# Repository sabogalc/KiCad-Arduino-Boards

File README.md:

# KiCad Arduino Boards

## Introduction
This repository contains KiCad version 8 design files for eight different Arduino boards that have been recreated from scratch. I was first inspired to work on this project when I received an Arduino Uno R3 for a class project (which you can read [here](https://github.com/sabogalc/KiCad-Arduino-Boards/blob/main/Remote%20Temperature%20Monitoring%20Project.pdf)). Although I had never used an Arduino before, I found it quite useful and versatile. However, I wanted to make some changes to better suit my needs.

## Project Motivation
While working with the Arduino Uno R3, I was frustrated by the need for a USB-B printer cable to use it. Since the Arduino hardware is open source, I decided to recreate the board with a USB-C connector. Additionally, I learned that Arduino boards are not made in KiCad, so I figured this project could also have another benefit in making the designs more open and accessible. Although buying an R4 Minima that already comes with USB-C would have been easier and less expensive, I enjoyed the challenge of re-designing the board myself.

## Design Process
Every Adruino board I could find is made in either EAGLE or Altium, and KiCad has importers for both of these formats. However, importing designs always comes with a level of artifacting and other inaccuracies. The effort to correct the imports would be comparable to remaking the board from scratch, so I opted for the latter since it would produce a cleaner end result. 

Given the popularity and open-source nature of Arduino boards, I assumed that partial or complete KiCad versions might already exist. The following repositories were helpful for getting started:
- [Arduino Uno R3 From Scratch](https://github.com/rheingoldheavy/arduino_uno_r3_from_scratch): Schematic and BOM
- [Arduino Uno KiCad Template](https://github.com/Jeff-Russ/Arduino_Uno_Template): Bare board layout
- [Arduino UNO R3 BOM](https://gist.github.com/yahyatawil/ee6ad731bcf5a5b37dcf2cac04245fbe): BOM only

Even with these resources, I had to find a reset switch footprint myself, but eventually I landed on a compatible one with the TS06-667-30-BK-100-G-SMT-TR by CUI Devices. I now had every piece I needed to make a schematic and PCB, and while doing the PCB layout I would consistently reference the imported design and try to make the component placement and routing as close to the original as possible.

## Visual Comparison
Below is a comparison of the imported UNO R3 board and my completed board, highlighting the differences and benefits in re-making the board from scratch. The most apparent differences are in the silkscreen labeling and the included 3D models of the components:

## Boards Included
This repository includes designs for:
- Arduino Uno R3
- Arduino Uno R3 SMD
- Arduino Uno R4 Minima
- Arduino Uno R4 WiFi (this one may have some issues; see its folder for details)
- Arduino Leonardo
- Arduino Micro
- Arduino Nano
- Arduino Mega 2560

For details about each board, refer to the `README` file in their respective folders.

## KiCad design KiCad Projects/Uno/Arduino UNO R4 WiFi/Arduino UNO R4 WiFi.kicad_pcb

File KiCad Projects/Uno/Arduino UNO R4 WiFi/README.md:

# UNO R4 WiFi
I am not the same man I was before making this board.

As soon as I saw the 96 LED array on this board, I knew that I would be in for some work, and of all the boards in this repository, this is the only one that I am not confident would pass a fabricator's specifications. I will highlight the parts of this board that I think may be problematic below.

Firstly, the 3.3V fuse is extremely close to a GND pad on the USB-C port, which could be a possible weak point for a 3.3V short to GND to happen.

Next of course is the placement and routing of the LEDs, especially because lots of these tracks have very little clearance between them.

Some of the curved traces on this board may also be problematic, like in the example below.

All in all, if anyone does actually order the gerbers for this board, please let me know if either all is well or if there are corrections that need to be made.

Below are the screenshots of this board from KiCad's 3D board viewer.

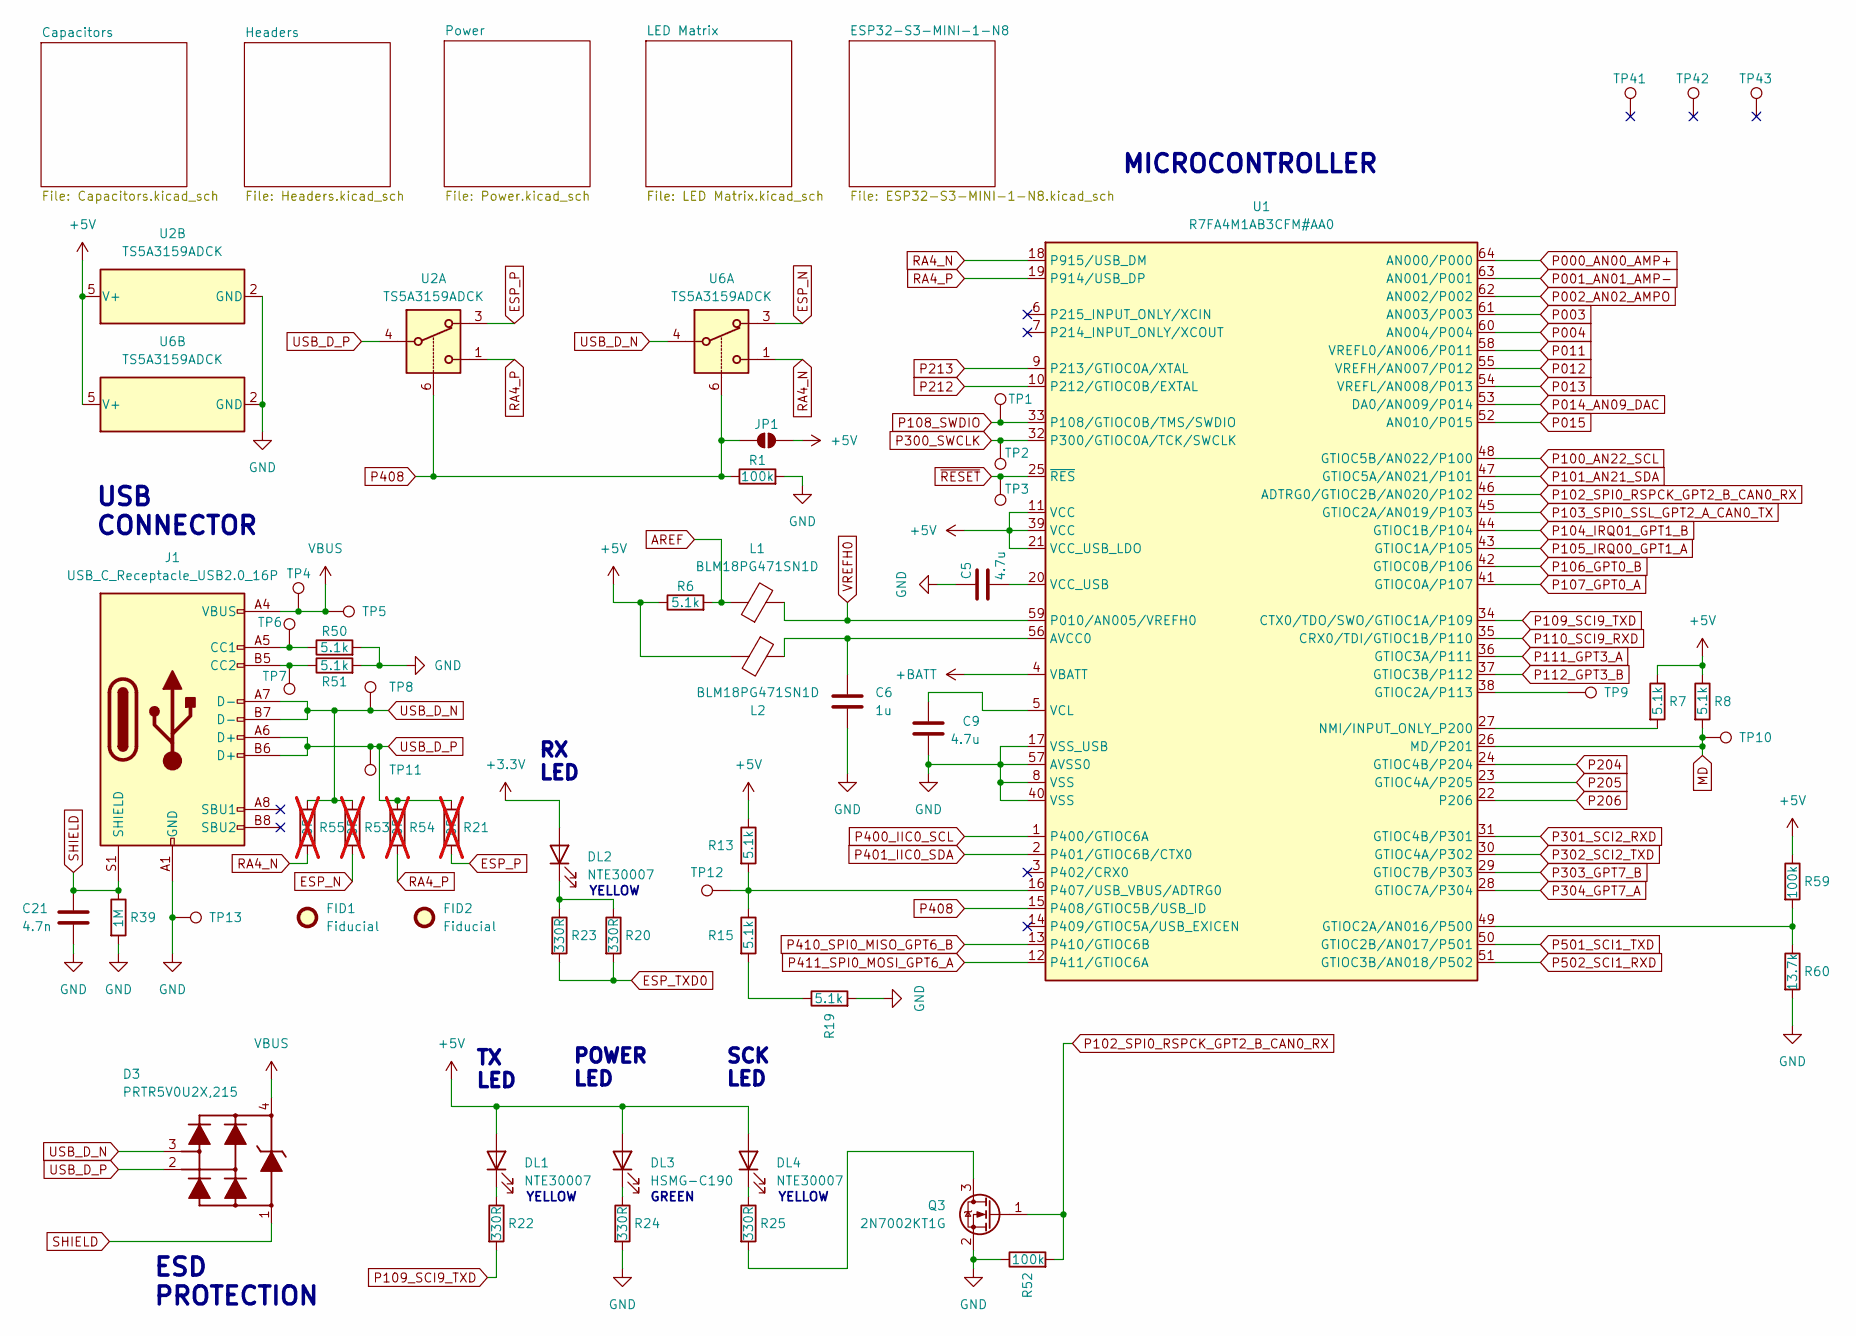
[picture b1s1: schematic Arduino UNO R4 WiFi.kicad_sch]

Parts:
C5, C9: 4.7u; C_0603_1608Metric
C6: 1u; C_0402_1005Metric
C21: 4.7n; C_0805_2012Metric
D3: PRTR5V0U2X,215; SOT-143
DL1, DL2, DL4: NTE30007; LED_0603_1608Metric
DL3: HSMG-C190; LED_0603_1608Metric
FID1, FID2: Fiducial; Fiducial_1mm_Mask2mm
J1: USB_C_Receptacle_USB2.0_16P; USB_C_Receptacle_GCT_USB4105-xx-A_16P_TopMnt_Horizontal
JP1: SolderJumper_2_Open; SolderJumper-2_P1.3mm_Open_Pad1.0x1.5mm
L1, L2: BLM18PG471SN1D; L_0603_1608Metric
Q3: 2N7002KT1G; SC-59
R1, R52, R59: 100k; R_0402_1005Metric
R6, R7, R8, R13, R15, R19, R50, R51: 5.1k; R_0402_1005Metric
R20, R22, R23, R24, R25: 330R; R_0402_1005Metric
R21, R53, R54, R55: 0R; R_0402_1005Metric; not fitted
R39: 1M; R_0402_1005Metric
R60: 13.7k; R_0402_1005Metric
TP1, TP2, TP3, TP4, TP6, TP7, TP10, TP12: TestPoint; TestPoint_Pad_D0.8mm
TP5, TP8, TP11, TP13, TP41, TP42, TP43: TestPoint; TestPoint_Pad_D1.0mm
TP9: TestPoint; TestPoint_P113
U1: R7FA4M1AB3CFM#AA0; LQFP-64_10x10mm_P0.5mm
U2, U6: TS5A3159ADCK; SOT-363_SC-70-6

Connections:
+3.3V: DL2.2 (A); also elsewhere on the board
+5V: DL1.2 (A), DL3.2 (A), DL4.2 (A), JP1.2 (B), L2.2, R6.1, R7.1, R8.1, R13.1, R59.1, U1.11 (VCC), U1.21 (VCC_USB_LDO), U1.39 (VCC), U2.5 (V+), U6.5 (V+); also elsewhere on the board
+BATT: U1.4 (VBATT); also elsewhere on the board
AREF: L1.1, R6.2; also elsewhere on the board
ESP_N: R53.2, U6.3; also elsewhere on the board
ESP_P: R21.2, U2.3; also elsewhere on the board
ESP_TXD0: R20.2, R23.2; also elsewhere on the board
GND: C5.2, C6.2, C9.1, C21.2, J1.A1 (GND), J1.A12 (GND), J1.B1 (GND), J1.B12 (GND), Q3.2 (S), R1.2, R19.2, R24.2, R39.2, R50.2, R51.2, R52.1, R60.2, TP13.1, U1.8 (VSS), U1.17 (VSS_USB), U1.40 (VSS), U1.57 (AVSS0), U2.2 (GND), U6.2 (GND); also elsewhere on the board
MD: R8.2, TP10.1, U1.26 (MD/P201); also elsewhere on the board
unnamed: DL1.1 (K), R22.1
unnamed: DL2.1 (K), R20.1, R23.1
unnamed: DL3.1 (K), R24.1
unnamed: DL4.1 (K), R25.1
unnamed: J1.A5 (CC1), R50.1, TP6.1
unnamed: J1.B5 (CC2), R51.1, TP7.1
unnamed: Q3.3 (D), R25.2
unnamed: R15.2, R19.1
unnamed: C6.1, L2.1, U1.56 (AVCC0)
unnamed: R59.2, R60.1, U1.49 (GTIOC2A/AN016/P500)
unnamed: TP9.1, U1.38 (GTIOC2A/P113)
unnamed: R7.2, U1.27 (NMI/INPUT_ONLY_P200)
unnamed: R13.2, R15.1, TP12.1, U1.16 (P407/USB_VBUS/ADTRG0)
unnamed: C5.1, U1.20 (VCC_USB)
unnamed: C9.2, U1.5 (VCL)
P000_AN00_AMP+: U1.64 (AN000/P000); also elsewhere on the board
P001_AN01_AMP-: U1.63 (AN001/P001); also elsewhere on the board
P002_AN02_AMPO: U1.62 (AN002/P002); also elsewhere on the board
P003: U1.61 (AN003/P003); also elsewhere on the board
P004: U1.60 (AN004/P004); also elsewhere on the board
P011: U1.58 (VREFL0/AN006/P011); also elsewhere on the board
P012: U1.55 (VREFH/AN007/P012); also elsewhere on the board
P013: U1.54 (VREFL/AN008/P013); also elsewhere on the board
P014_AN09_DAC: U1.53 (DA0/AN009/P014); also elsewhere on the board
P015: U1.52 (AN010/P015); also elsewhere on the board
P100_AN22_SCL: U1.48 (GTIOC5B/AN022/P100); also elsewhere on the board
P101_AN21_SDA: U1.47 (GTIOC5A/AN021/P101); also elsewhere on the board
P102_SPI0_RSPCK_GPT2_B_CAN0_RX: Q3.1 (G), R52.2, U1.46 (ADTRG0/GTIOC2B/AN020/P102); also elsewhere on the board
P103_SPI0_SSL_GPT2_A_CAN0_TX: U1.45 (GTIOC2A/AN019/P103); also elsewhere on the board
P104_IRQ01_GPT1_B: U1.44 (GTIOC1B/P104); also elsewhere on the board
P105_IRQ00_GPT1_A: U1.43 (GTIOC1A/P105); also elsewhere on the board
P106_GPT0_B: U1.42 (GTIOC0B/P106); also elsewhere on the board
P107_GPT0_A: U1.41 (GTIOC0A/P107); also elsewhere on the board
P108_SWDIO: TP1.1, U1.33 (P108/GTIOC0B/TMS/SWDIO); also elsewhere on the board
P109_SCI9_TXD: R22.2, U1.34 (CTX0/TDO/SWO/GTIOC1A/P109); also elsewhere on the board
P110_SCI9_RXD: U1.35 (CRX0/TDI/GTIOC1B/P110); also elsewhere on the board
P111_GPT3_A: U1.36 (GTIOC3A/P111); also elsewhere on the board
P112_GPT3_B: U1.37 (GTIOC3B/P112); also elsewhere on the board
P204: U1.24 (GTIOC4B/P204); also elsewhere on the board
P205: U1.23 (GTIOC4A/P205); also elsewhere on the board
P206: U1.22 (P206); also elsewhere on the board
P212: U1.10 (P212/GTIOC0B/EXTAL); also elsewhere on the board
P213: U1.9 (P213/GTIOC0A/XTAL); also elsewhere on the board
P300_SWCLK: TP2.1, U1.32 (P300/GTIOC0A/TCK/SWCLK); also elsewhere on the board
P301_SCI2_RXD: U1.31 (GTIOC4B/P301); also elsewhere on the board
P302_SCI2_TXD: U1.30 (GTIOC4A/P302); also elsewhere on the board
P303_GPT7_B: U1.29 (GTIOC7B/P303); also elsewhere on the board
P304_GPT7_A: U1.28 (GTIOC7A/P304); also elsewhere on the board
P400_IIC0_SCL: U1.1 (P400/GTIOC6A); also elsewhere on the board
P401_IIC0_SDA: U1.2 (P401/GTIOC6B/CTX0); also elsewhere on the board
P408: JP1.1 (A), R1.1, U1.15 (P408/GTIOC5B/USB_ID), U2.6, U6.6
P410_SPI0_MISO_GPT6_B: U1.13 (P410/GTIOC6B); also elsewhere on the board
P411_SPI0_MOSI_GPT6_A: U1.12 (P411/GTIOC6A); also elsewhere on the board
P501_SCI1_TXD: U1.50 (GTIOC2B/AN017/P501); also elsewhere on the board
P502_SCI1_RXD: U1.51 (GTIOC3B/AN018/P502); also elsewhere on the board
RA4_N: R55.2, U1.18 (P915/USB_DM), U6.1
RA4_P: R54.2, U1.19 (P914/USB_DP), U2.1
SHIELD: C21.1, D3.1, J1.S1 (SHIELD), R39.1
USB_D_N: D3.3, J1.A7 (D-), J1.B7 (D-), R53.1, R55.1, TP8.1, U6.4
USB_D_P: D3.2, J1.A6 (D+), J1.B6 (D+), R21.1, R54.1, TP11.1, U2.4
VBUS: D3.4, J1.A4 (VBUS), J1.A9 (VBUS), J1.B4 (VBUS), J1.B9 (VBUS), TP4.1, TP5.1; also elsewhere on the board
VREFH0: L1.2, U1.59 (P010/AN005/VREFH0); also elsewhere on the board
~RESET: TP3.1, U1.25 (~RES); also elsewhere on the board

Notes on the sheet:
TX LED
GREEN
USB CONNECTOR
SCK LED
YELLOW
ESD PROTECTION
POWER LED
RX LED
MICROCONTROLLER

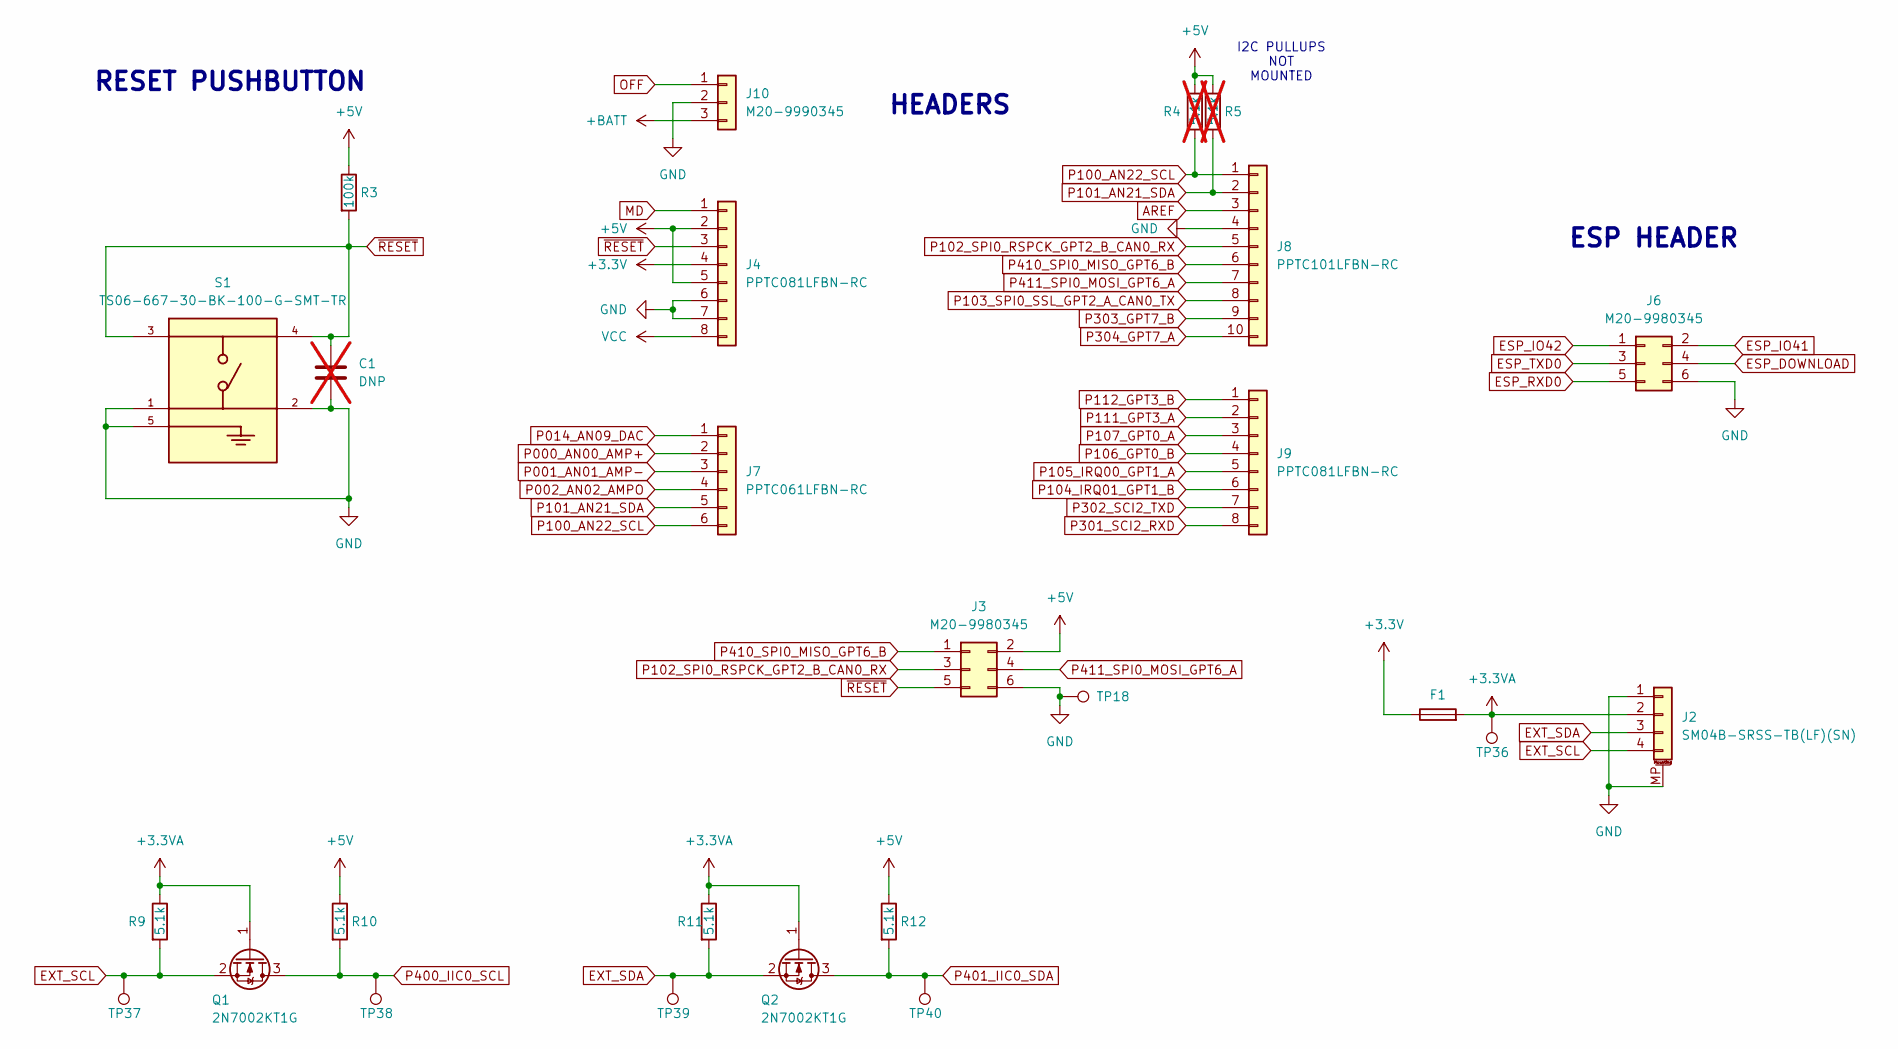
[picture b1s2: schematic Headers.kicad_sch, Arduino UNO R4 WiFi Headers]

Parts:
C1: DNP; C_0402_1005Metric; not fitted
F1: MF-MSMF050-2-W2; Fuse_1812_4532Metric
J2: SM04B-SRSS-TB(LF)(SN); JST_SH_SM04B-SRSS-TB_1x04-1MP_P1.00mm_Horizontal
J3, J6: M20-9980345; PinHeader_2x03_P2.54mm_Vertical
J4, J9: PPTC081LFBN-RC; PinSocket_1x08_P2.54mm_Vertical
J7: PPTC061LFBN-RC; PinSocket_1x06_P2.54mm_Vertical
J8: PPTC101LFBN-RC; PinSocket_1x10_P2.54mm_Vertical
J10: M20-9990345; PinHeader_1x03_P2.54mm_Vertical
Q1, Q2: 2N7002KT1G; SC-59
R3: 100k; R_0402_1005Metric
R4, R5: 5.1k; R_0402_1005Metric; not fitted
R9, R10, R11, R12: 5.1k; R_0402_1005Metric
S1: TS06-667-30-BK-100-G-SMT-TR; SW_TS06-667-30-BK-100-G-SMT-TR; PARTREV 1.0
TP18: TestPoint; TestPoint_Pad_D1.0mm
TP36, TP37, TP38, TP39, TP40: TestPoint; TestPoint_Pad_D0.8mm

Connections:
+3.3V: F1.1, J4.4; also elsewhere on the board
+3.3VA: F1.2, J2.2, Q1.1 (G), Q2.1 (G), R9.1, R11.1, TP36.1
+5V: J3.2, J4.2, J4.5, R3.1, R4.1, R5.1, R10.1, R12.1; also elsewhere on the board
+BATT: J10.3; also elsewhere on the board
AREF: J8.3; also elsewhere on the board
ESP_DOWNLOAD: J6.4; also elsewhere on the board
ESP_IO41: J6.2; also elsewhere on the board
ESP_IO42: J6.1; also elsewhere on the board
ESP_RXD0: J6.5; also elsewhere on the board
ESP_TXD0: J6.3; also elsewhere on the board
EXT_SCL: J2.4, Q1.2 (S), R9.2, TP37.1
EXT_SDA: J2.3, Q2.2 (S), R11.2, TP39.1
GND: C1.2, J2.1, J2.MP (MountPin), J3.6, J4.6, J4.7, J6.6, J8.4, J10.2, S1.1, S1.2, S1.5, TP18.1; also elsewhere on the board
MD: J4.1; also elsewhere on the board
OFF: J10.1; also elsewhere on the board
P000_AN00_AMP+: J7.2; also elsewhere on the board
P001_AN01_AMP-: J7.3; also elsewhere on the board
P002_AN02_AMPO: J7.4; also elsewhere on the board
P014_AN09_DAC: J7.1; also elsewhere on the board
P100_AN22_SCL: J7.6, J8.1, R4.2; also elsewhere on the board
P101_AN21_SDA: J7.5, J8.2, R5.2; also elsewhere on the board
P102_SPI0_RSPCK_GPT2_B_CAN0_RX: J3.3, J8.5; also elsewhere on the board
P103_SPI0_SSL_GPT2_A_CAN0_TX: J8.8; also elsewhere on the board
P104_IRQ01_GPT1_B: J9.6; also elsewhere on the board
P105_IRQ00_GPT1_A: J9.5; also elsewhere on the board
P106_GPT0_B: J9.4; also elsewhere on the board
P107_GPT0_A: J9.3; also elsewhere on the board
P111_GPT3_A: J9.2; also elsewhere on the board
P112_GPT3_B: J9.1; also elsewhere on the board
P301_SCI2_RXD: J9.8; also elsewhere on the board
P302_SCI2_TXD: J9.7; also elsewhere on the board
P303_GPT7_B: J8.9; also elsewhere on the board
P304_GPT7_A: J8.10; also elsewhere on the board
P400_IIC0_SCL: Q1.3 (D), R10.2, TP38.1; also elsewhere on the board
P401_IIC0_SDA: Q2.3 (D), R12.2, TP40.1; also elsewhere on the board
P410_SPI0_MISO_GPT6_B: J3.1, J8.6; also elsewhere on the board
P411_SPI0_MOSI_GPT6_A: J3.4, J8.7; also elsewhere on the board
VCC: J4.8; also elsewhere on the board
~RESET: C1.1, J3.5, J4.3, R3.2, S1.3, S1.4; also elsewhere on the board

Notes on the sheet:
RESET PUSHBUTTON
ESP HEADER
I2C PULLUPS NOT MOUNTED
HEADERS

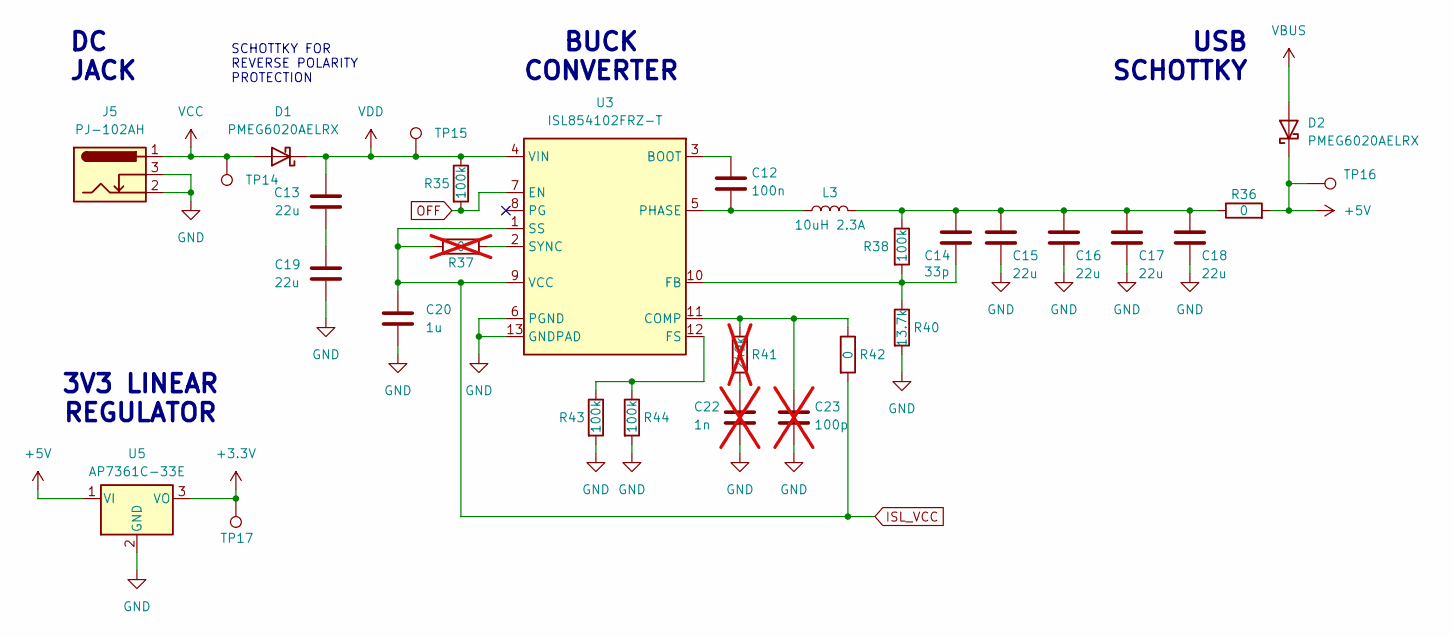
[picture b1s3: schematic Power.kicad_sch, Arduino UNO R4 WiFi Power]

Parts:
C12: 100n; C_0402_1005Metric
C13, C15, C16, C17, C18, C19: 22u; C_0805_2012Metric
C14: 33p; C_0402_1005Metric
C20: 1u; C_0402_1005Metric
C22: 1n; C_0402_1005Metric; not fitted
C23: 100p; C_0402_1005Metric; not fitted
D1, D2: PMEG6020AELRX; D_SOD-123
J5: PJ-102AH; BarrelJack_Kycon_KLDX-0202-xC_Horizontal
L3: 10uH 2.3A; PMF42-103MN
R35, R38, R43, R44: 100k; R_0402_1005Metric
R36, R42: 0; R_0402_1005Metric
R37: 0; R_0402_1005Metric; not fitted
R40: 13.7k; R_0402_1005Metric
R41: 249k; R_0402_1005Metric; not fitted
TP14: TestPoint; TestPoint_Pad_0.8mm
TP15, TP16, TP17: TestPoint; TestPoint_Pad_D0.8mm
U3: ISL854102FRZ-T; DFN-12-1EP_3x4mm_P0.5mm_EP1.7x3.3mm
U5: AP7361C-33E; SOT-223-3_TabPin2

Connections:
+3.3V: TP17.1, U5.3 (VO); also elsewhere on the board
+5V: D2.1 (K), R36.2, TP16.1, U5.1 (VI); also elsewhere on the board
GND: C15.2, C16.2, C17.2, C18.2, C19.2, C20.2, C22.2, C23.2, J5.2, J5.3, R40.2, R43.2, R44.2, U3.6 (PGND), U3.13 (GNDPAD), U5.2 (GND); also elsewhere on the board
ISL_VCC: C20.1, R37.1, R42.2, U3.1 (SS), U3.9 (VCC)
unnamed: C13.1, C19.1
unnamed: C14.1, C15.1, C16.1, C17.1, C18.1, L3.2, R36.1, R38.1
unnamed: C22.1, R41.2
unnamed: C12.1, U3.3 (BOOT)
unnamed: C23.1, R41.1, R42.1, U3.11 (COMP)
unnamed: C14.2, R38.2, R40.1, U3.10 (FB)
unnamed: R43.1, R44.1, U3.12 (FS)
unnamed: C12.2, L3.1, U3.5 (PHASE)
unnamed: R37.2, U3.2 (SYNC)
OFF: R35.2, U3.7 (EN); also elsewhere on the board
VBUS: D2.2 (A); also elsewhere on the board
VCC: D1.2 (A), J5.1, TP14.1; also elsewhere on the board
VDD: C13.2, D1.1 (K), R35.1, TP15.1, U3.4 (VIN)

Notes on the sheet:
SCHOTTKY FOR REVERSE POLARITY PROTECTION
3V3 LINEAR REGULATOR
USB SCHOTTKY
BUCK CONVERTER
DC JACK

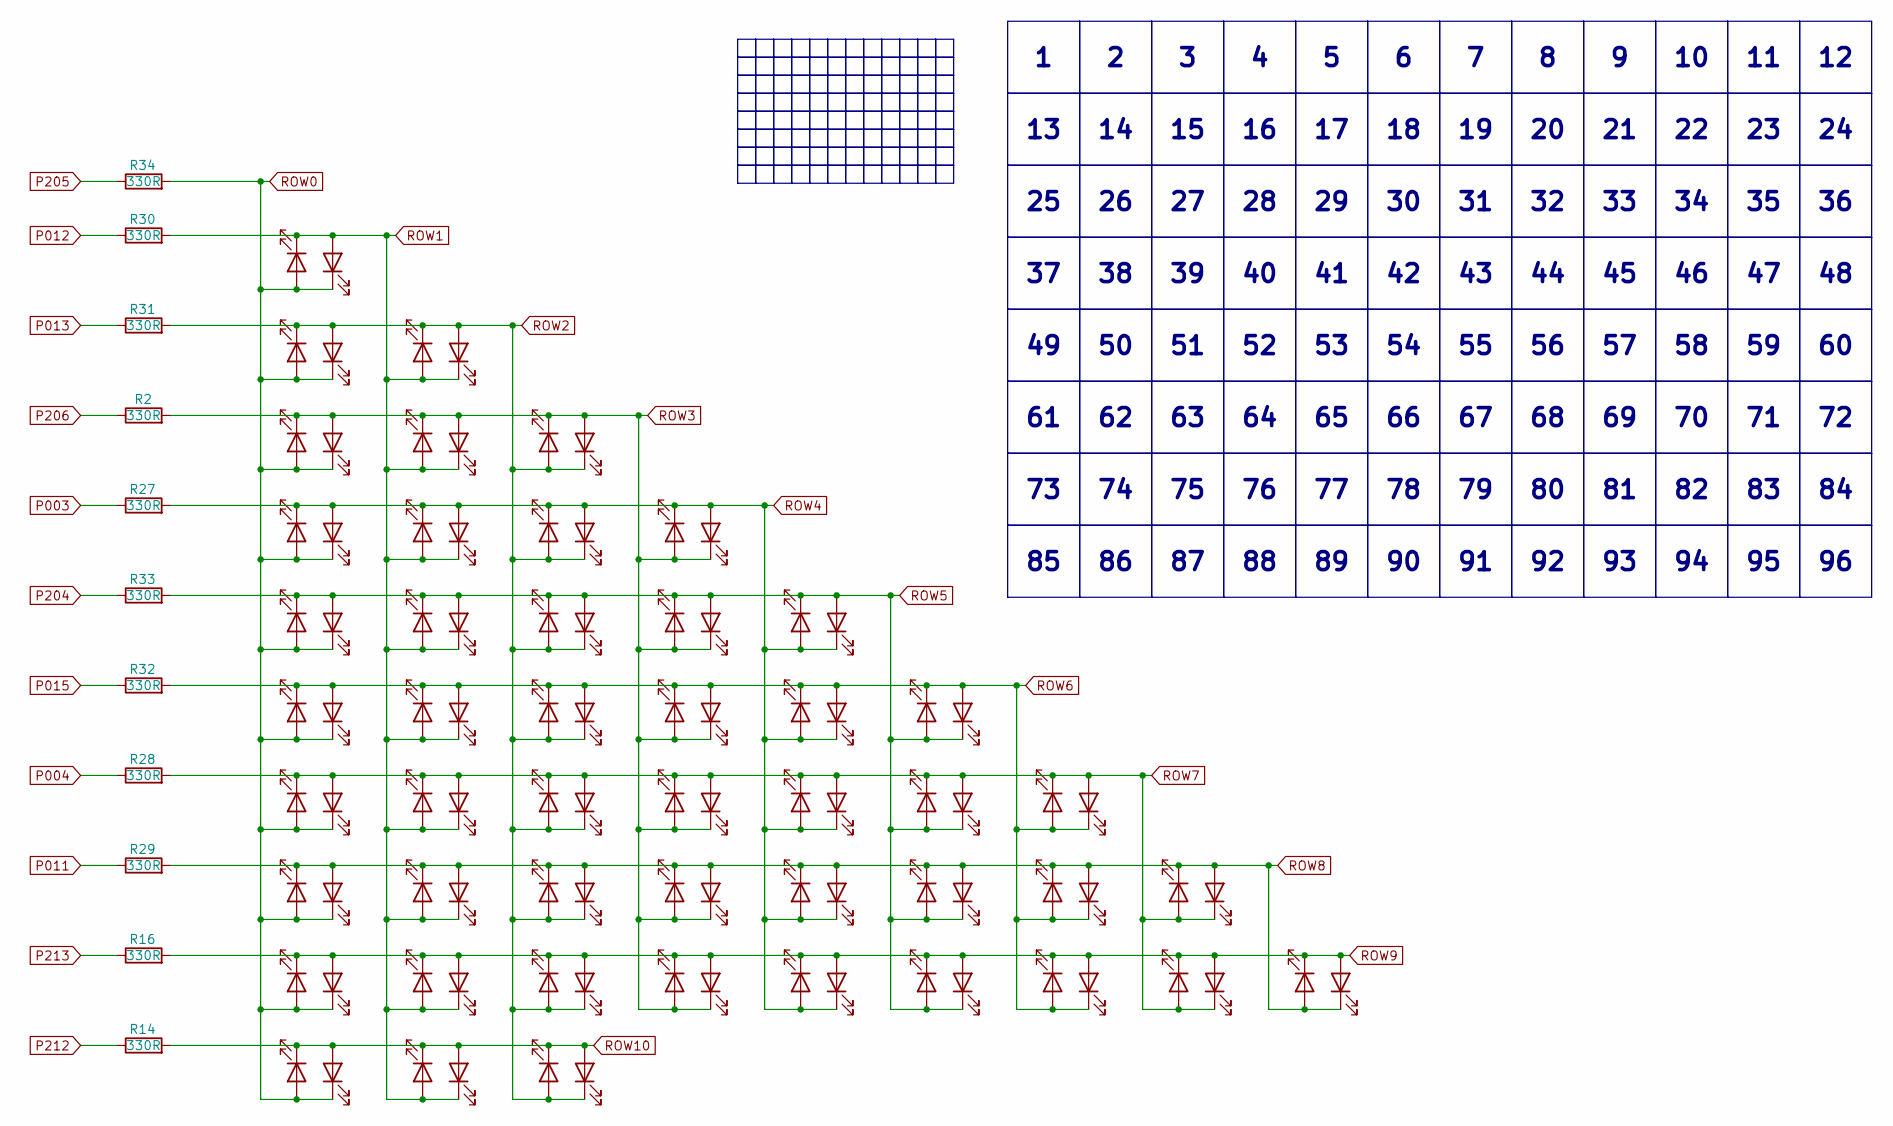
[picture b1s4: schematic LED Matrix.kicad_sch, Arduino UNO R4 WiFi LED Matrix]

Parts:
D01, D02, D03, D4, D5, D6, D7, D8, D9, D10, D11, D12, D13, D14, D15, D16, D17, D18, D19, D20, D21, D22, D23, D24, D25, D26, D27, D28, D29, D30, D31, D32, D33, D34, D35, D36, D37, D38, D39, D40, D41, D42, D43, D44, D45, D46, D47, D48, D49, D50, D51, D52, D53, D54, D55, D56, D57, D58, D59, D60, D61, D62, D63, D64, D65, D66, D67, D68, D69, D70, D71, D72, D73, D74, D75, D76, D77, D78, D79, D80, D81, D82, D83, D84, D85, D86, D87, D88, D89, D90, D91, D92, D93, D94, D95, D96: QBLP601-R5; LED_0603_1608Metric
R2, R14, R16, R27, R28, R29, R30, R31, R32, R33, R34: 330R; R_0402_1005Metric

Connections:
P003: R27.1; also elsewhere on the board
P004: R28.1; also elsewhere on the board
P011: R29.1; also elsewhere on the board
P012: R30.1; also elsewhere on the board
P013: R31.1; also elsewhere on the board
P015: R32.1; also elsewhere on the board
P204: R33.1; also elsewhere on the board
P205: R34.1; also elsewhere on the board
P206: R2.1; also elsewhere on the board
P212: R14.1; also elsewhere on the board
P213: R16.1; also elsewhere on the board
ROW0: D01.2 (A), D02.1 (K), D03.2 (A), D4.1 (K), D7.2 (A), D8.1 (K), D13.2 (A), D14.1 (K), D21.2 (A), D22.1 (K), D31.2 (A), D32.1 (K), D43.2 (A), D44.1 (K), D57.2 (A), D58.1 (K), D73.2 (A), D74.1 (K), D91.2 (A), D92.1 (K), R34.2
ROW1: D01.1 (K), D02.2 (A), D5.2 (A), D6.1 (K), D9.2 (A), D10.1 (K), D15.2 (A), D16.1 (K), D23.2 (A), D24.1 (K), D33.2 (A), D34.1 (K), D45.2 (A), D46.1 (K), D59.2 (A), D60.1 (K), D75.2 (A), D76.1 (K), D93.2 (A), D94.1 (K), R30.2
ROW2: D03.1 (K), D4.2 (A), D5.1 (K), D6.2 (A), D11.2 (A), D12.1 (K), D17.2 (A), D18.1 (K), D25.2 (A), D26.1 (K), D35.2 (A), D36.1 (K), D47.2 (A), D48.1 (K), D61.2 (A), D62.1 (K), D77.2 (A), D78.1 (K), D95.2 (A), D96.1 (K), R31.2
ROW3: D7.1 (K), D8.2 (A), D9.1 (K), D10.2 (A), D11.1 (K), D12.2 (A), D19.2 (A), D20.1 (K), D27.2 (A), D28.1 (K), D37.2 (A), D38.1 (K), D49.2 (A), D50.1 (K), D63.2 (A), D64.1 (K), D79.2 (A), D80.1 (K), R2.2
ROW4: D13.1 (K), D14.2 (A), D15.1 (K), D16.2 (A), D17.1 (K), D18.2 (A), D19.1 (K), D20.2 (A), D29.2 (A), D30.1 (K), D39.2 (A), D40.1 (K), D51.2 (A), D52.1 (K), D65.2 (A), D66.1 (K), D81.2 (A), D82.1 (K), R27.2
ROW5: D21.1 (K), D22.2 (A), D23.1 (K), D24.2 (A), D25.1 (K), D26.2 (A), D27.1 (K), D28.2 (A), D29.1 (K), D30.2 (A), D41.2 (A), D42.1 (K), D53.2 (A), D54.1 (K), D67.2 (A), D68.1 (K), D83.2 (A), D84.1 (K), R33.2
ROW6: D31.1 (K), D32.2 (A), D33.1 (K), D34.2 (A), D35.1 (K), D36.2 (A), D37.1 (K), D38.2 (A), D39.1 (K), D40.2 (A), D41.1 (K), D42.2 (A), D55.2 (A), D56.1 (K), D69.2 (A), D70.1 (K), D85.2 (A), D86.1 (K), R32.2
ROW7: D43.1 (K), D44.2 (A), D45.1 (K), D46.2 (A), D47.1 (K), D48.2 (A), D49.1 (K), D50.2 (A), D51.1 (K), D52.2 (A), D53.1 (K), D54.2 (A), D55.1 (K), D56.2 (A), D71.2 (A), D72.1 (K), D87.2 (A), D88.1 (K), R28.2
ROW8: D57.1 (K), D58.2 (A), D59.1 (K), D60.2 (A), D61.1 (K), D62.2 (A), D63.1 (K), D64.2 (A), D65.1 (K), D66.2 (A), D67.1 (K), D68.2 (A), D69.1 (K), D70.2 (A), D71.1 (K), D72.2 (A), D89.2 (A), D90.1 (K), R29.2
ROW9: D73.1 (K), D74.2 (A), D75.1 (K), D76.2 (A), D77.1 (K), D78.2 (A), D79.1 (K), D80.2 (A), D81.1 (K), D82.2 (A), D83.1 (K), D84.2 (A), D85.1 (K), D86.2 (A), D87.1 (K), D88.2 (A), D89.1 (K), D90.2 (A), R16.2
ROW10: D91.1 (K), D92.2 (A), D93.1 (K), D94.2 (A), D95.1 (K), D96.2 (A), R14.2

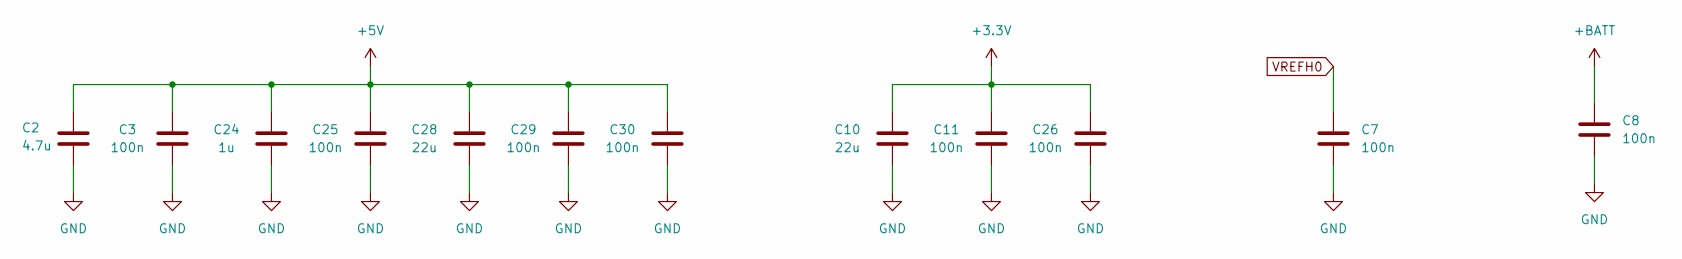
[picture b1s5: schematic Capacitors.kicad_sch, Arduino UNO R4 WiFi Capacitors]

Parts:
C2: 4.7u; C_0603_1608Metric
C3, C7, C8, C11, C25, C26, C29, C30: 100n; C_0402_1005Metric
C10, C28: 22u; C_0805_2012Metric
C24: 1u; C_0402_1005Metric

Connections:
+3.3V: C10.1, C11.1, C26.1; also elsewhere on the board
+5V: C2.1, C3.1, C24.1, C25.1, C28.1, C29.1, C30.1; also elsewhere on the board
+BATT: C8.1; also elsewhere on the board
GND: C2.2, C3.2, C7.2, C8.2, C10.2, C11.2, C24.2, C25.2, C26.2, C28.2, C29.2, C30.2; also elsewhere on the board
VREFH0: C7.1; also elsewhere on the board

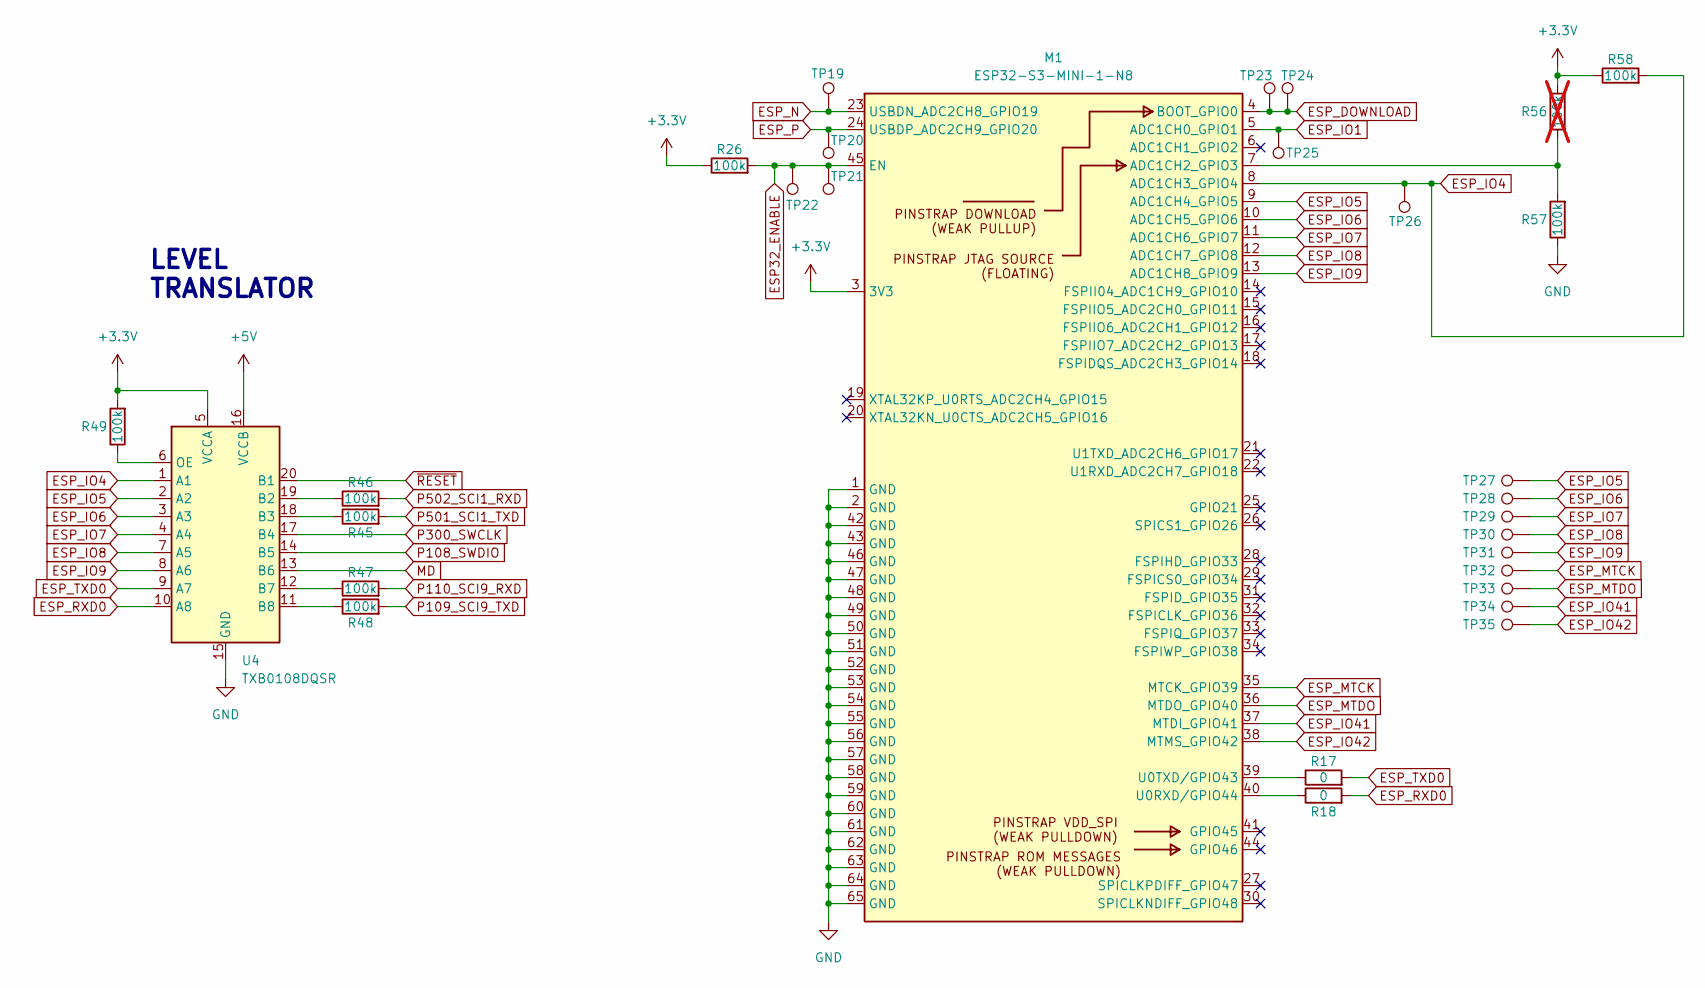
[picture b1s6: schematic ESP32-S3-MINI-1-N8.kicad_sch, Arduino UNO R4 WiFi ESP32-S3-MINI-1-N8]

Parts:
M1: ESP32-S3-MINI-1-N8; XCVR_ESP32-S3-MINI-1-N8
R17, R18: 0; R_0402_1005Metric
R26, R45, R46, R47, R48, R49, R57, R58: 100k; R_0402_1005Metric
R56: 100k; R_0402_1005Metric; not fitted
TP19, TP20, TP21, TP23, TP25, TP26, TP27, TP28, TP29, TP30, TP31, TP32, TP33, TP34, TP35: TestPoint; TestPoint_Pad_D0.8mm
TP22, TP24: TestPoint; TestPoint_Pad_D1.0mm
U4: TXB0108DQSR; USON-20_2x4mm_P0.4mm

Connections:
+3.3V: M1.3 (3V3), R26.1, R49.2, R56.2, R58.1, U4.5 (VCCA); also elsewhere on the board
+5V: U4.16 (VCCB); also elsewhere on the board
ESP32_ENABLE: M1.45 (EN), R26.2, TP21.1, TP22.1
ESP_DOWNLOAD: M1.4 (BOOT_GPIO0), TP23.1, TP24.1; also elsewhere on the board
ESP_IO1: M1.5 (ADC1CH0_GPIO1), TP25.1
ESP_IO4: M1.8 (ADC1CH3_GPIO4), R58.2, TP26.1, U4.1 (A1)
ESP_IO5: M1.9 (ADC1CH4_GPIO5), TP27.1, U4.2 (A2)
ESP_IO6: M1.10 (ADC1CH5_GPIO6), TP28.1, U4.3 (A3)
ESP_IO7: M1.11 (ADC1CH6_GPIO7), TP29.1, U4.4 (A4)
ESP_IO8: M1.12 (ADC1CH7_GPIO8), TP30.1, U4.7 (A5)
ESP_IO9: M1.13 (ADC1CH8_GPIO9), TP31.1, U4.8 (A6)
ESP_IO41: M1.37 (MTDI_GPIO41), TP34.1; also elsewhere on the board
ESP_IO42: M1.38 (MTMS_GPIO42), TP35.1; also elsewhere on the board
ESP_MTCK: M1.35 (MTCK_GPIO39), TP32.1
ESP_MTDO: M1.36 (MTDO_GPIO40), TP33.1
ESP_N: M1.23 (USBDN_ADC2CH8_GPIO19), TP19.1; also elsewhere on the board
ESP_P: M1.24 (USBDP_ADC2CH9_GPIO20), TP20.1; also elsewhere on the board
ESP_RXD0: R18.2, U4.10 (A8); also elsewhere on the board
ESP_TXD0: R17.2, U4.9 (A7); also elsewhere on the board
GND: M1.1 (GND), M1.2 (GND), M1.42 (GND), M1.43 (GND), M1.46 (GND), M1.47 (GND), M1.48 (GND), M1.49 (GND), M1.50 (GND), M1.51 (GND), M1.52 (GND), M1.53 (GND), M1.54 (GND), M1.55 (GND), M1.56 (GND), M1.57 (GND), M1.58 (GND), M1.59 (GND), M1.60 (GND), M1.61 (GND), M1.62 (GND), M1.63 (GND), M1.64 (GND), M1.65 (GND), R57.1, U4.15 (GND); also elsewhere on the board
MD: U4.13 (B6); also elsewhere on the board
unnamed: M1.7 (ADC1CH2_GPIO3), R56.1, R57.2
unnamed: M1.40 (U0RXD/GPIO44), R18.1
unnamed: M1.39 (U0TXD/GPIO43), R17.1
unnamed: R46.1, U4.19 (B2)
unnamed: R45.1, U4.18 (B3)
unnamed: R47.1, U4.12 (B7)
unnamed: R48.1, U4.11 (B8)
unnamed: R49.1, U4.6 (OE)
P108_SWDIO: U4.14 (B5); also elsewhere on the board
P109_SCI9_TXD: R48.2; also elsewhere on the board
P110_SCI9_RXD: R47.2; also elsewhere on the board
P300_SWCLK: U4.17 (B4); also elsewhere on the board
P501_SCI1_TXD: R45.2; also elsewhere on the board
P502_SCI1_RXD: R46.2; also elsewhere on the board
~RESET: U4.20 (B1); also elsewhere on the board

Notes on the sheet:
LEVEL TRANSLATOR
